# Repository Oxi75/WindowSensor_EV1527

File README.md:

# WindowSensor_EV1527

This project enables the integration of affordable 433 MHz window sensors and push buttons into the **homee** smart home system via **vhih**.

## Hardware

- **ESP32** microcontroller
- **EV1527** 433 MHz receiver module

## Features

- Receives signals from standard 433 MHz window sensors and push buttons (EV1527 protocol)
- Forwards sensor states to homee via vhih
- Simple configuration through a web interface

## Installation

1. Assemble the hardware according to the schematic (ESP32 + EV1527 receiver).
2. compile and flash the nano firmware [PlatformIO](https://platformio.org/).
3. compile and flash the ESP32 firmware 
4. Connect the device to Wi-Fi and configure it via the web interface.

## Directory Structure

- `src/` – Project source code
- `include/` – Header files
- `data/` – Web interface files (e.g., configuration)
- `examples/` – Example projects
- `doku/` – user manual
- `KiCad/` – Schematics and PCB layout

## Notes

- Further information about integrating with homee and vhih can be found in the documentation and source code.
- License: See [LICENSE](LICENSE)

---

Window and door sensor for homee, based on EV1527 and ESP32.

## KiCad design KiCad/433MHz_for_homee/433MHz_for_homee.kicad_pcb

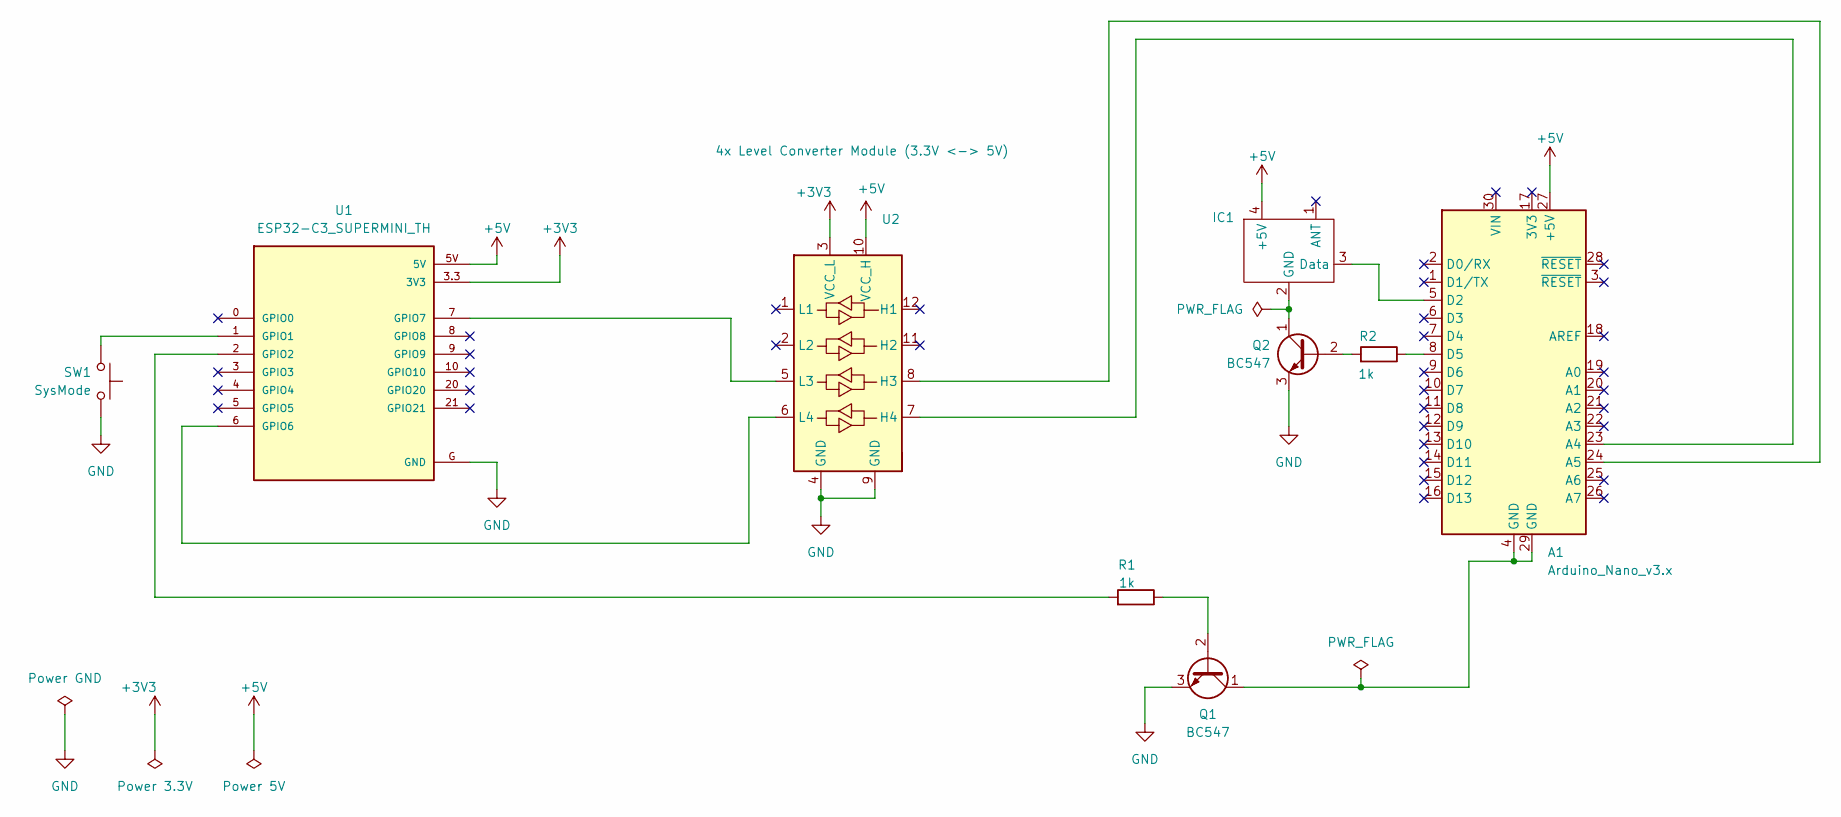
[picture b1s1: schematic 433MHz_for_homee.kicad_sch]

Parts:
A1: Arduino_Nano_v3.x; Arduino_Nano
IC1: rxb14_433MHz_module
Q1, Q2: BC547; TO-92_Inline
R1, R2: 1k; R_0805_2012Metric_Pad1.20x1.40mm_HandSolder
SW1: SysMode; PinHeader_1x02_P2.54mm_Vertical
U1: ESP32-C3_SUPERMINI_TH; MODULE_ESP32-C3_SUPERMINI_TH
U2: 4x Level Converter Module (3.3V <-> 5V); LevelConverter_MH

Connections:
+3V3: U1.3.3 (3V3), U2.3 (VCC_L)
+5V: A1.27 (+5V), IC1.4 (+5V), U1.5V, U2.10 (VCC_H)
GND: Q1.3 (E), Q2.3 (E), SW1.1, U1.G (GND), U2.4 (GND), U2.9 (GND)
unnamed: A1.23 (A4), U2.7 (H4)
unnamed: A1.24 (A5), U2.8 (H3)
unnamed: A1.5 (D2), IC1.3 (Data)
unnamed: A1.8 (D5), R2.1
unnamed: IC1.2 (GND), Q2.1 (C)
unnamed: Q1.2 (B), R1.1
unnamed: A1.4 (GND), A1.29 (GND), Q1.1 (C)
unnamed: Q2.2 (B), R2.2
unnamed: SW1.2, U1.1 (GPIO1)
unnamed: R1.2, U1.2 (GPIO2)
unnamed: U1.6 (GPIO6), U2.6 (L4)
unnamed: U1.7 (GPIO7), U2.5 (L3)

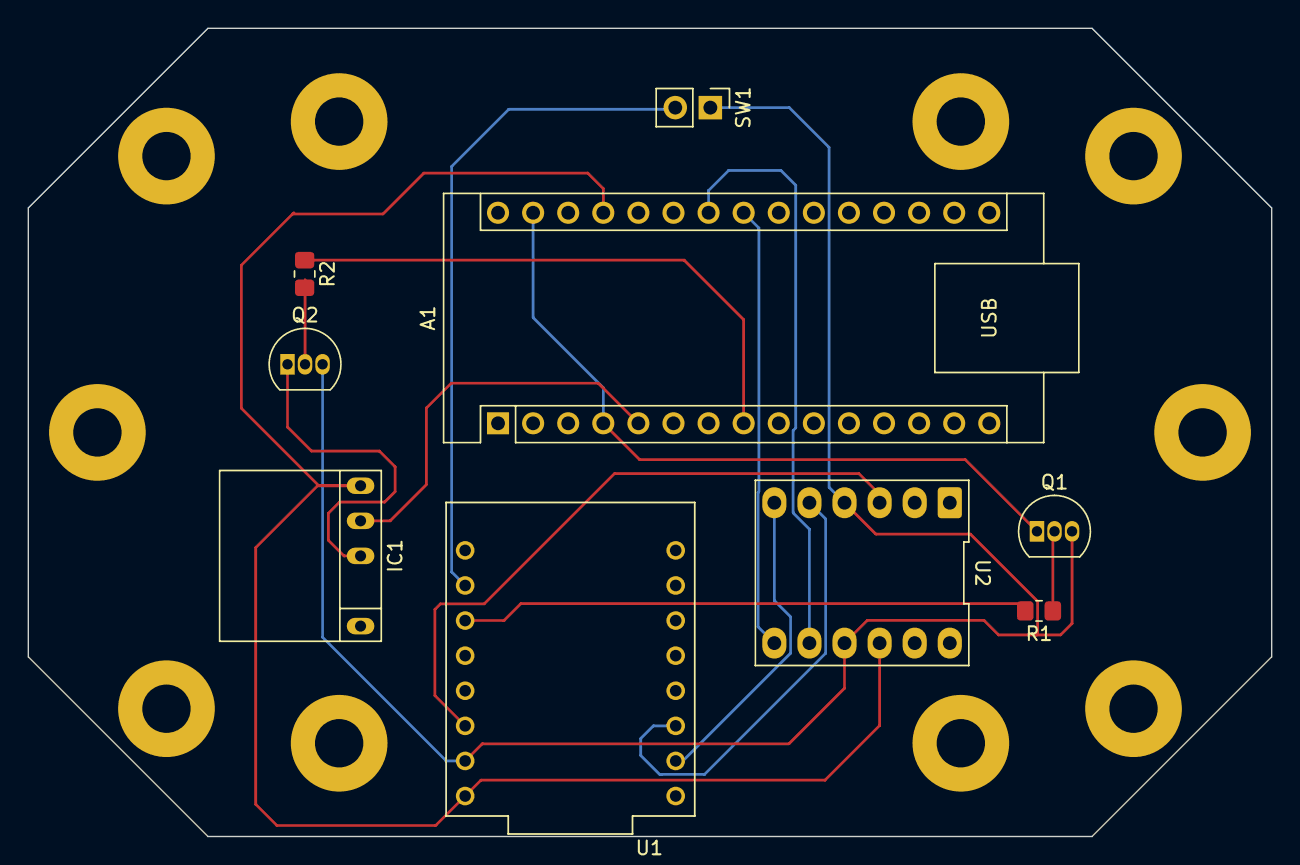
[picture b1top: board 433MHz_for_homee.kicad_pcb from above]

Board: 2 copper layers, 90.0 x 58.5 mm, 9 parts (0 on the bottom side), 15 nets.

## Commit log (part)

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2025-05-31 working basically
2025-06-01 added function to show last received transmission in config interface
2025-06-04 extended to PushButton, and auto-Release function for misc signals - compiles but not yet tested
2025-06-04 Webinterface and config-manager updated. Backend pending.
2025-06-04 Cosmetical changes in WebUI
2025-06-05 updated but not yet functional
2025-06-05 compiles again and receives transmissions from the sensor. Config part needs to be adapted and homee to be tested
2025-06-05 config saving still not correct
2025-06-06 saving and loading of configuration seems to work now
2025-06-06 improved signal-reset by timestamp but probably added some new issues
2025-06-11 - power cycle of receiver module on startup - modified processing of received signals
2025-06-12 GPIO changed, Webserver only in APMode, explicit reset of singnal attributes -> works better but still not stable
2025-06-18 renamed main.cpp to main_ESP32.cpp added main_Arduino.cpp modified platformio.ini
2025-06-18 improved debugging on Arduino-Side + debugging deaktivated prepared power on for Arduino on ESP side
2025-06-18 ESP32 updated, compiles but not yet tested
2025-06-19 Arduino: fixed timing for debug mode on / off ESP32: limited I2C requests to less than 4times per sec
2025-06-19 configuration works, receiving works, transmission to ESP works, Sensors and signals are detected properly, auto-release works
2025-06-19 cosmetical changes on config UI
2025-06-20 fixed an issue with re-importing a config file
2025-06-20 OTA Update works now
2025-06-20 modifictions in platformio.ini and related defines to support ESP32-C3-SuperMini Board
2025-06-22 KiCAD Project added
2025-06-27 fixed an issue that prevents saving more then four sensor configurations
2025-06-29 added index.html as read-only configuration display
2025-06-30 added ability to webinterface to download and update html files
2025-06-30 fixed button colors on web interface
2025-06-30 fixed issues with download / upload index.html
2025-07-05 moved #debug to global defines
2025-07-06 Revert "moved #debug to global defines"
    This reverts commit b1c320d95064f0c7cb145d6277651185ba752029.
2025-07-06 updated web-interface with new toggle-parameter + updated C-Backend. Not yet tested.
2025-07-07 fixed some JSON issues
2025-07-07 fixed a JSON size bug
2025-07-07 fixed a bug in the PCB
2025-07-17 changed battery level to battery alarm for OpenClose-Sensors.
2025-07-20 added additional attribute that shows the sensor address in homee
2025-07-26 fixed some addressing bugs
2025-07-26 User manual updated
2025-07-26 set link to github
